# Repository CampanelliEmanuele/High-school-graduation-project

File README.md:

# Table of contents

- [High-school-graduation-project](#high-school-graduation-project)
  - [Nucleo del progetto](#nucleo-del-progetto)
  - [Documentazione del progetto](#documentazione-del-progetto)
    - [Presentazione dell'elaborato](#presentazione-dellelaborato)
    - [Relazione dell'elaborato](#relazione-dellelaborato)
  - [Codice del progetto](#codice-del-progetto)
    - [Cartella coi codici](#cartella-coi-codici)
  - [Schemi del progetto](#schemi-del-progetto)
    - [Sbrogliato finale](#sbrogliato-finale)
    - [Schema elettrico finale](#schema-elettrico-finale)
    - [Diagramma degli stati](#diagramma-degli-stati)
    - [Diagramma di flusso completo](#diagramma-di-flusso-completo)
    - [Integrazioni](#integrazioni)
      - [Sbrogliato: shift register](#sbrogliato-shift-register)
      - [Schema elettrico: NE555 in PWM](#schema-elettrico-ne555-in-pwm)

# High-school-graduation-project

## Nucleo del progetto

Il progetto portato all'esame di maturità consisteva in un prototipo di una centralina per il controllo di un motore DC con l'aggiunta di eventuali modifiche e integrazioni.
Per ulteriori approfondimenti consiglio di visionare i vari PDF, uno dei quali contiene dei link, oramai non più funzionanti, di immagini e schemi ma presenti (e raggiungibili) nelle varie cartelle.

## Documentazione del progetto

#### [Presentazione dell'elaborato](./PDFs/Presentazione-elaborato.pdf)

#### [Relazione dell'elaborato](./PDFs/Relazione-elaborato.pdf)

## Codice del progetto

#### [Cartella coi codici](./Materiale-dell-elaborato/Programma-centralina/)

## Schemi del progetto

### Sbrogliato finale

### Schema elettrico finale

### Diagramma degli stati

### Diagramma di flusso completo

### Integrazioni

#### Sbrogliato: shift register

#### Schema elettrico: NE555 in PWM

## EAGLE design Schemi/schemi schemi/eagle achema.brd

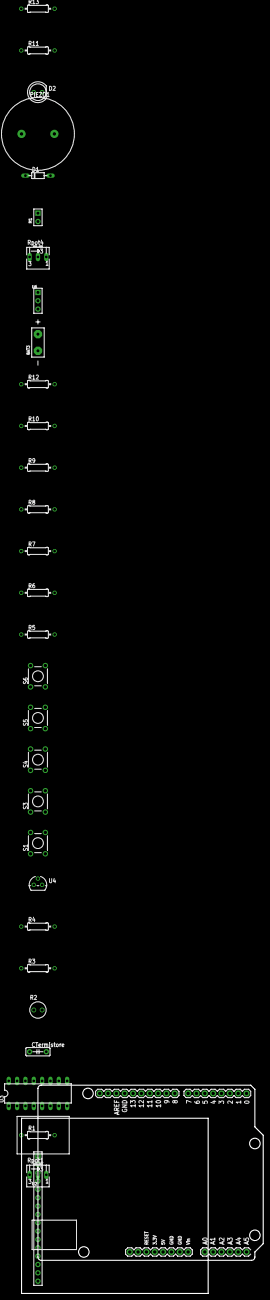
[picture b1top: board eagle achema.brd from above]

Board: 2 copper layers, 73.6 x 63.4 mm, 31 parts (0 on the bottom side), 33 nets, no tracks yet.

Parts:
BAT3: DC-POWER
CTermistore: 100nF; C5B2.5
D1: D-7.5
D2: LED5MM
M1: 2P-2.54-65/35MIL
PIEZO1: PIEZO-22MM
R1: 220‎Ω; 0207/10
R2: PHOTORESISTOR-2.54
R3, R4, R5: 1k‎Ω; 0207/10
R6: 1M‎Ω; 0207/10
R7, R8, R9, R10, R12: 4700‎Ω; 0207/10
R11, R13: 100‎Ω; 0207/10
Rpot1, Rpot4: 250k‎Ω; B25V
S1, S3, S4, S5, S6: TL1105
U1: ARDUINO_UNO
U2: 1X16P-2.54-2.54-11.6-3.0-BLACK-MALE
U3: DIL16
U4: TO92
U6: 1X3P-2.54-2.54-11.6-3.0-BLACK-MALE

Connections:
unnamed: Rpot1.S, U2.3
unnamed: R1.2, U2.15
unnamed: R2.P$1, R3.2
unnamed: CTermistore.1, R1.1, R2.P$2, Rpot1.A, Rpot4.A, S1.3, U1.5V, U1.A0, U2.2, U3.8, U4.2, U6.2
unnamed: R10.2, R12.1, S4.1
unnamed: R6.1, S3.4, S4.4, S5.4, S6.4, U1.A2
unnamed: R7.2, R8.2, S3.1
unnamed: R8.1, R9.1, S6.1
unnamed: R9.2, R10.1, S5.1
unnamed: R6.2, R7.1
unnamed: U1.9, U4.3
unnamed: R5.2, S1.4, U1.8
unnamed: U1.10, U6.1
unnamed: Rpot4.S, U1.A1
unnamed: CTermistore.2, R4.2, U1.A3
unnamed: U1.7, U2.4
unnamed: U1.6, U2.6
unnamed: U1.4, U2.12
unnamed: U1.3, U2.13
unnamed: U1.2, U2.14
unnamed: U1.5, U2.11
unnamed: U1.11, U3.1
unnamed: U1.12, U3.2
unnamed: D1.C, M1.2, U3.3
unnamed: D1.A, M1.1, U3.6
unnamed: U1.13, U3.7
unnamed: BAT3.-, R3.1, R4.1, R5.1, Rpot1.E, Rpot4.E, U1.GND.., U2.1, U2.5, U2.16, U3.4, U3.5, U3.12, U3.13, U4.1, U6.3
unnamed: BAT3.+, U3.16
unnamed: PIEZO1.P$1, R11.2
unnamed: D2.K, PIEZO1.P$2, U1.GND.
unnamed: D2.A, R13.2
unnamed: R11.1, U1.A5
unnamed: R13.1, U1.A4

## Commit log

2021-09-19 chore: code cleanup
2023-09-13 Add: First PDFs
2023-09-13 Add: all files
2023-10-06 Update: README.md
2023-10-06 Chore: folders and files rename
2023-10-06 Add: new folder
